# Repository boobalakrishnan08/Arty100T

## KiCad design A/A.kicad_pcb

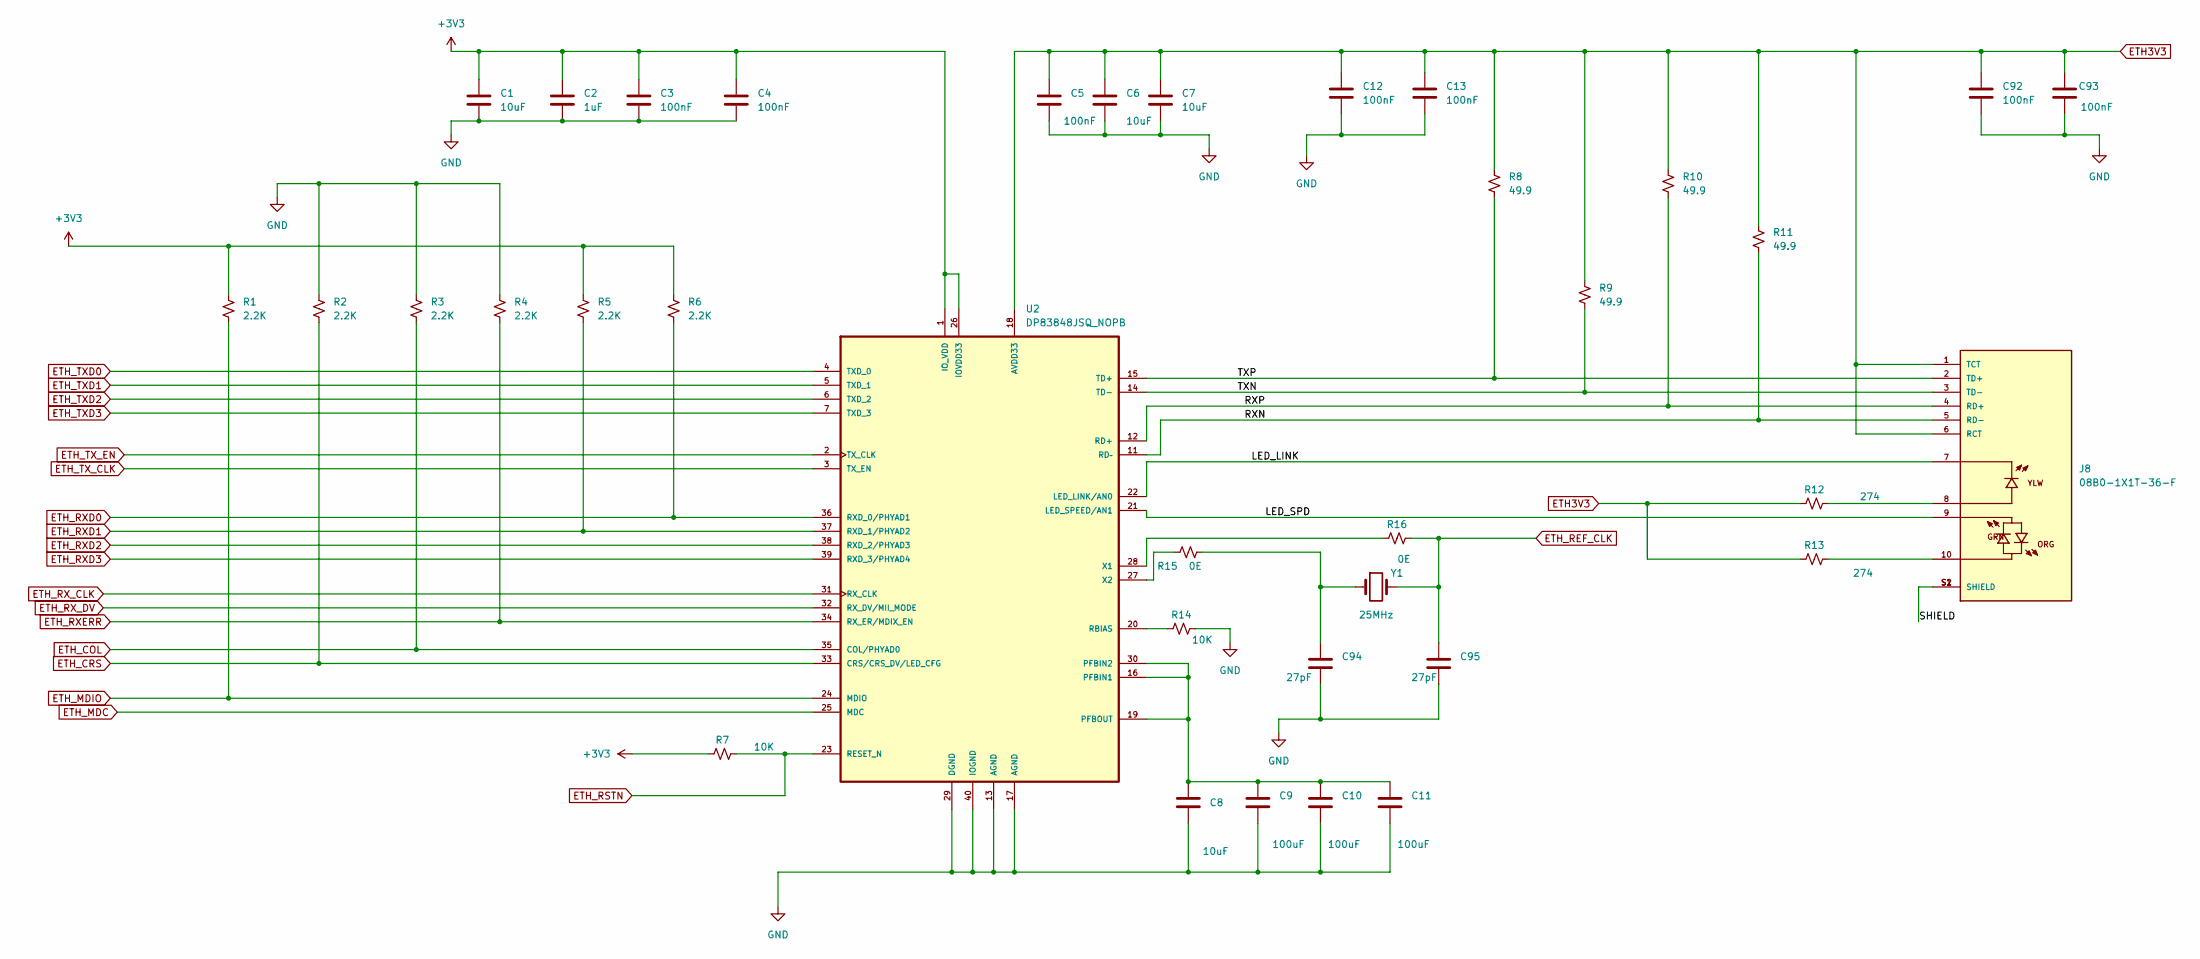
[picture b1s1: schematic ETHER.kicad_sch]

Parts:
C1: 10uF; C_1206_3216Metric
C2: 1uF; C_0805_2012Metric
C3, C4, C5, C12, C13, C92, C93: 100nF; C_1206_3216Metric
C6, C7, C8: 10uF; C_0805_2012Metric
C9, C10, C11: 100uF; C_1206_3216Metric
C94, C95: 27pF; C_0603_1608Metric
J8: 08B0-1X1T-36-F; BEL_08B0-1X1T-36-F; PARTREV D
R1, R2, R3, R4, R5, R6: 2.2K; R_0402_1005Metric
R7, R14: 10K; R_0402_1005Metric
R8, R9, R10, R11: 49.9; R_0402_1005Metric
R12, R13: 274; R_0402_1005Metric
R15, R16: 0E; R_0402_1005Metric
U2: DP83848JSQ_NOPB; XCVR_DP83848JSQ_NOPB; PARTREV APR 2015; DigiKey_Part_Number DP83848JSQ/NOPBTR-ND
Y1: 25MHz; Crystal_SMD_SeikoEpson_FA128-4Pin_2.0x1.6mm

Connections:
+3V3: C1.1, C2.1, C3.1, C4.1, R1.1, R5.1, R6.1, R7.1, U2.1 (IO_VDD), U2.26 (IOVDD33); also elsewhere on the board
/ETHER/LED_LINK: J8.7, U2.22 (LED_LINK/AN0)
/ETHER/LED_SPD: J8.9, U2.21 (LED_SPEED/AN1)
/ETHER/RXN: J8.5 (RD-), R11.2, U2.11 (RD–)
/ETHER/RXP: J8.4 (RD+), R10.2, U2.12 (RD+)
/ETHER/SHIELD: J8.S1 (SHIELD), J8.S2 (SHIELD)
/ETHER/TXN: J8.3 (TD-), R9.2, U2.14 (TD-)
/ETHER/TXP: J8.2 (TD+), R8.2, U2.15 (TD+)
ETH3V3: C5.1, C6.1, C7.1, C12.1, C13.1, C92.1, C93.1, J8.1 (TCT), J8.6 (RCT), R8.1, R9.1, R10.1, R11.1, R12.1, R13.1, U2.18 (AVDD33)
ETH_COL: R3.2, U2.35 (COL/PHYAD0); also elsewhere on the board
ETH_CRS: R2.2, U2.33 (CRS/CRS_DV/LED_CFG); also elsewhere on the board
ETH_MDC: U2.25 (MDC); also elsewhere on the board
ETH_MDIO: R1.2, U2.24 (MDIO); also elsewhere on the board
ETH_REF_CLK: C95.1, R16.2, Y1.2; also elsewhere on the board
ETH_RSTN: R7.2, U2.23 (RESET_N); also elsewhere on the board
ETH_RXD0: R6.2, U2.36 (RXD_0/PHYAD1); also elsewhere on the board
ETH_RXD1: R5.2, U2.37 (RXD_1/PHYAD2); also elsewhere on the board
ETH_RXD2: U2.38 (RXD_2/PHYAD3); also elsewhere on the board
ETH_RXD3: U2.39 (RXD_3/PHYAD4); also elsewhere on the board
ETH_RXERR: R4.2, U2.34 (RX_ER/MDIX_EN); also elsewhere on the board
ETH_RX_CLK: U2.31 (RX_CLK); also elsewhere on the board
ETH_RX_DV: U2.32 (RX_DV/MII_MODE); also elsewhere on the board
ETH_TXD0: U2.4 (TXD_0); also elsewhere on the board
ETH_TXD1: U2.5 (TXD_1); also elsewhere on the board
ETH_TXD2: U2.6 (TXD_2); also elsewhere on the board
ETH_TXD3: U2.7 (TXD_3); also elsewhere on the board
ETH_TX_CLK: U2.3 (TX_EN); also elsewhere on the board
ETH_TX_EN: U2.2 (TX_CLK); also elsewhere on the board
GND: C1.2, C2.2, C3.2, C4.2, C5.2, C6.2, C7.2, C8.2, C9.2, C10.2, C11.2, C12.2, C13.2, C92.2, C93.2, C94.2, C95.2, R2.1, R3.1, R4.1, R14.2, U2.13 (AGND), U2.17 (AGND), U2.29 (DGND), U2.40 (IOGND); also elsewhere on the board
unnamed: C94.1, R15.2, Y1.1
unnamed: J8.8, R12.2
unnamed: J8.10, R13.2
unnamed: C8.1, C9.1, C10.1, C11.1, U2.16 (PFBIN1), U2.19 (PFBOUT), U2.30 (PFBIN2)
unnamed: R14.1, U2.20 (RBIAS)
unnamed: R16.1, U2.28 (X1)
unnamed: R15.1, U2.27 (X2)

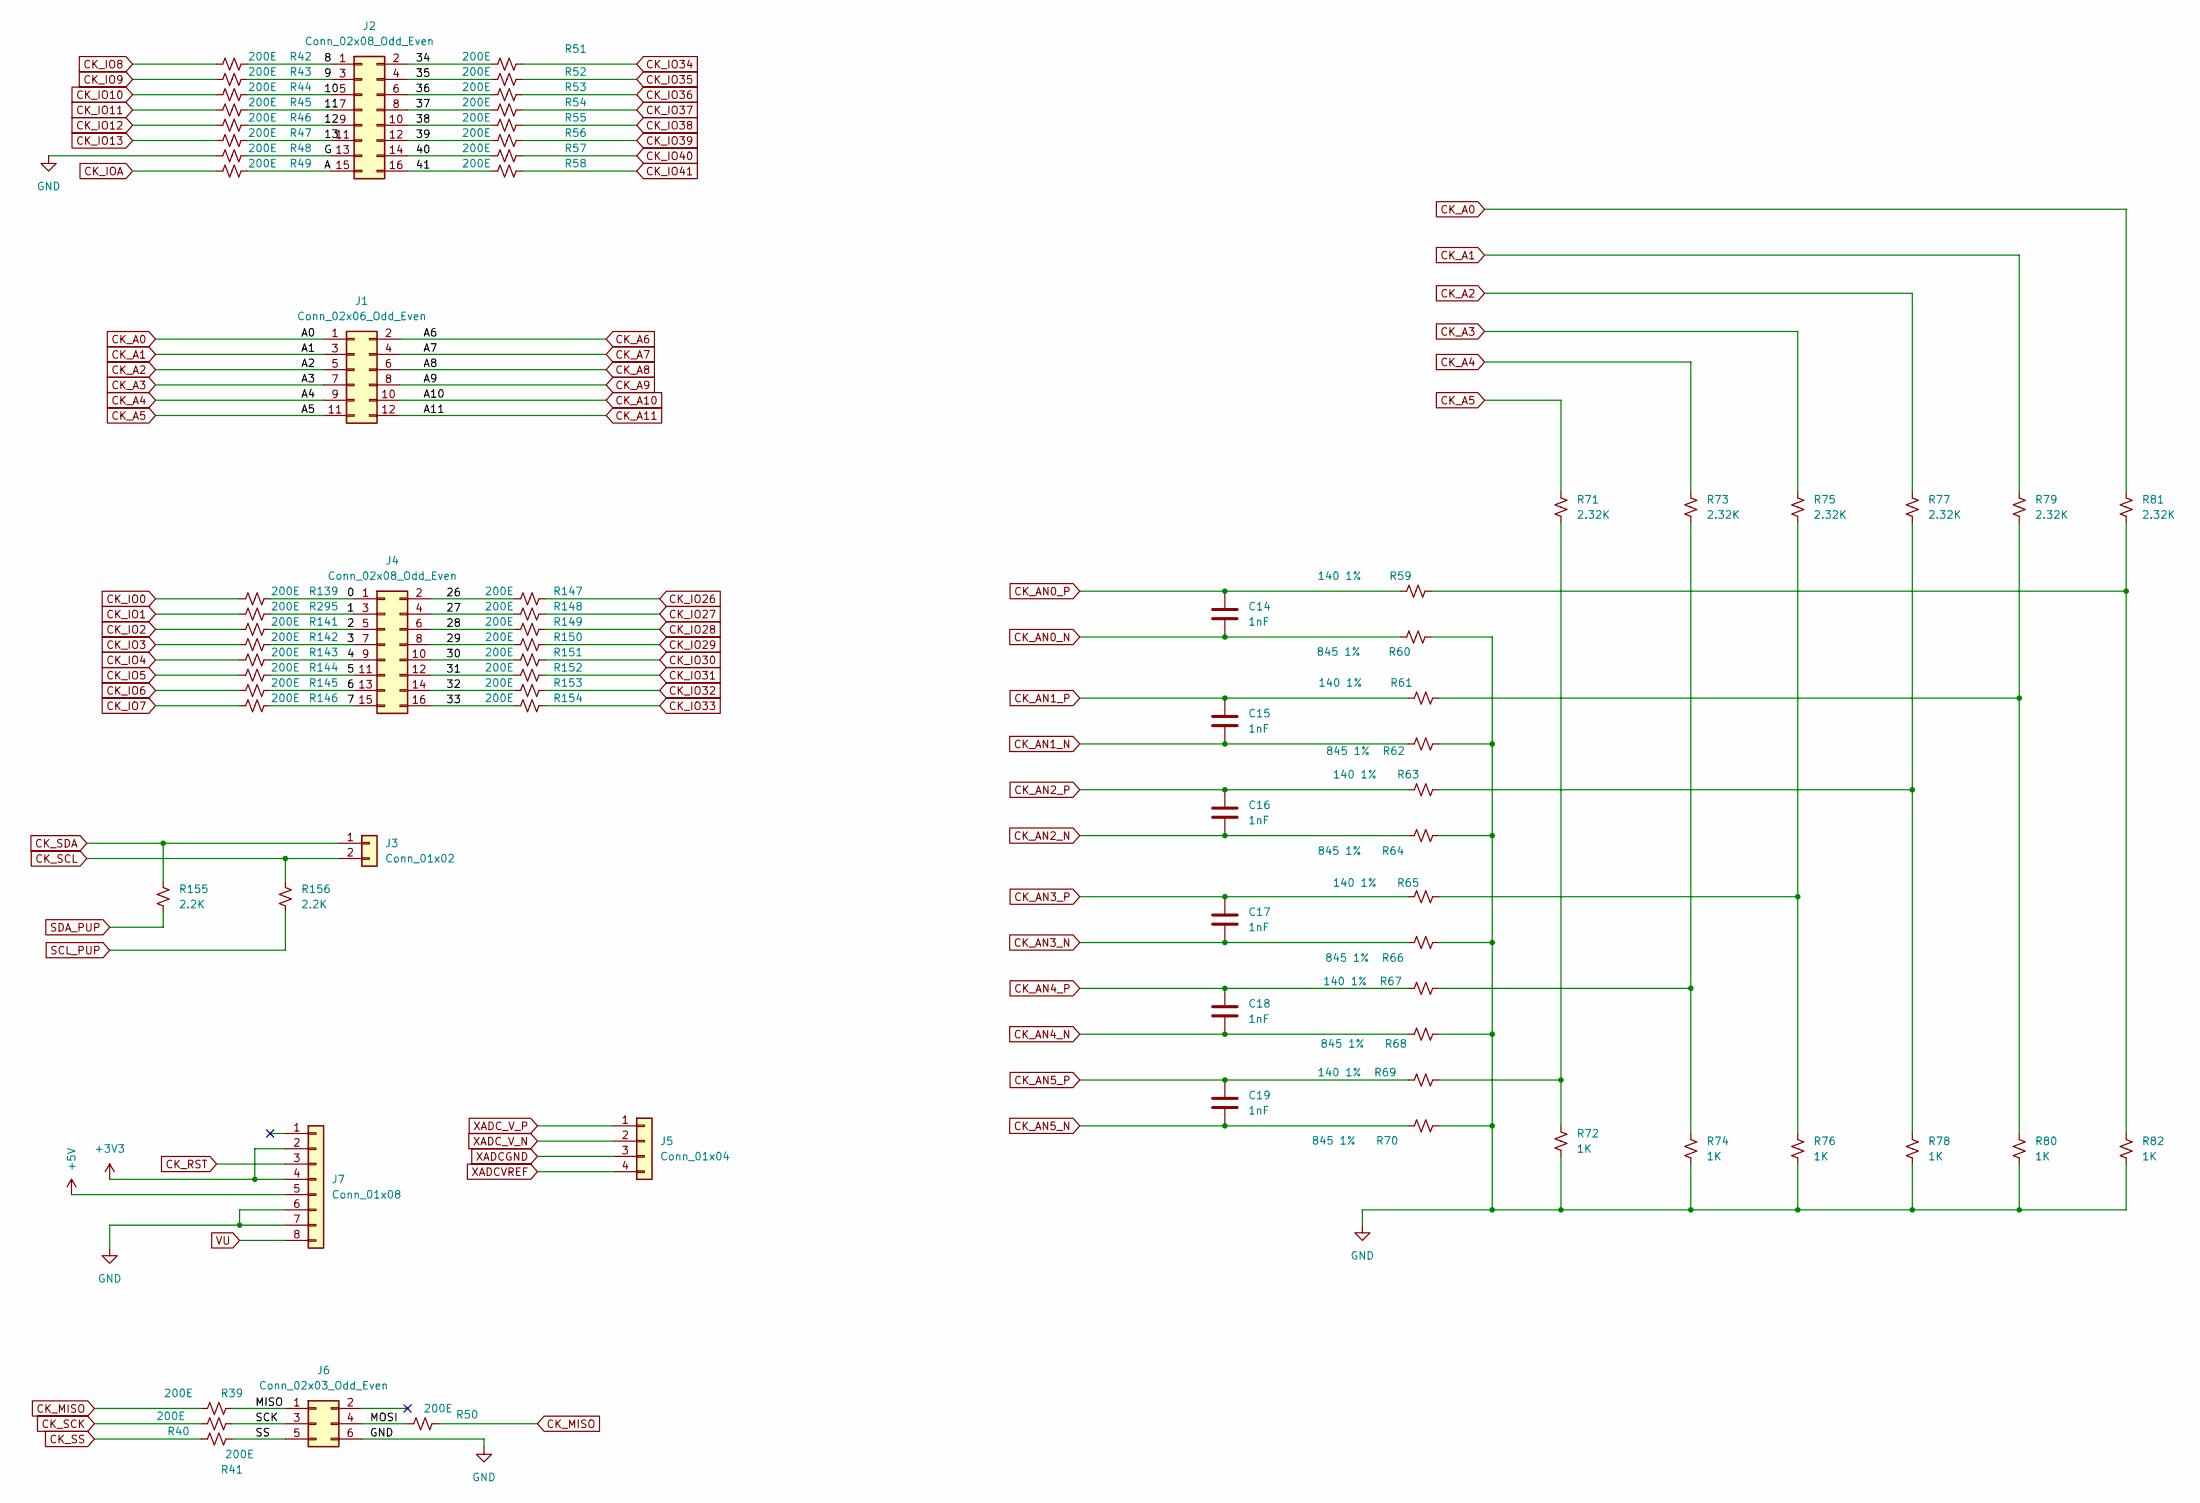
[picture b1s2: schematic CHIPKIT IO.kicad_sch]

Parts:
C14, C15, C16, C17, C18, C19: 1nF; C_0805_2012Metric
J1: Conn_02x06_Odd_Even; PinSocket_2x06_P2.54mm_Vertical
J2, J4: Conn_02x08_Odd_Even; PinSocket_2x08_P2.54mm_Vertical
J3: Conn_01x02; PinSocket_2x01_P2.54mm_Vertical
J5: Conn_01x04; PinSocket_1x04_P2.54mm_Vertical
J6: Conn_02x03_Odd_Even; PinSocket_2x03_P2.54mm_Vertical
J7: Conn_01x08; PinSocket_1x08_P2.54mm_Vertical
R39, R40, R41, R42, R43, R44, R45, R46, R47, R48, R49, R50, R51, R52, R53, R54, R55, R56, R57, R58, R139, R141, R142, R143, R144, R145, R146, R147, R148, R149, R150, R151, R152, R153, R154, R295: 200E; R_0402_1005Metric
R59, R61, R63, R65, R67, R69: 140 1%; R_0402_1005Metric
R60, R62, R64, R66, R68, R70: 845 1%; R_0402_1005Metric
R71, R73, R75, R77, R79, R81: 2.32K; R_0402_1005Metric
R72, R74, R76, R78, R80, R82: 1K; R_0402_1005Metric
R155, R156: 2.2K; R_0402_1005Metric

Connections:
+3V3: J7.2, J7.4; also elsewhere on the board
+5V: J7.5; also elsewhere on the board
/CHIPKIT IO/0: J4.1, R139.2
/CHIPKIT IO/1: J4.3, R295.2
/CHIPKIT IO/2: J4.5, R141.2
/CHIPKIT IO/3: J4.7, R142.2
/CHIPKIT IO/4: J4.9, R143.2
/CHIPKIT IO/5: J4.11, R144.2
/CHIPKIT IO/6: J4.13, R145.2
/CHIPKIT IO/7: J4.15, R146.2
/CHIPKIT IO/8: J2.1, R42.2
/CHIPKIT IO/9: J2.3, R43.2
/CHIPKIT IO/10: J2.5, R44.2
/CHIPKIT IO/11: J2.7, R45.2
/CHIPKIT IO/12: J2.9, R46.2
/CHIPKIT IO/13: J2.11, R47.2
/CHIPKIT IO/26: J4.2, R147.1
/CHIPKIT IO/27: J4.4, R148.1
/CHIPKIT IO/28: J4.6, R149.1
/CHIPKIT IO/29: J4.8, R150.1
/CHIPKIT IO/30: J4.10, R151.1
/CHIPKIT IO/31: J4.12, R152.1
/CHIPKIT IO/32: J4.14, R153.1
/CHIPKIT IO/33: J4.16, R154.1
/CHIPKIT IO/34: J2.2, R51.1
/CHIPKIT IO/35: J2.4, R52.1
/CHIPKIT IO/36: J2.6, R53.1
/CHIPKIT IO/37: J2.8, R54.1
/CHIPKIT IO/38: J2.10, R55.1
/CHIPKIT IO/39: J2.12, R56.1
/CHIPKIT IO/40: J2.14, R57.1
/CHIPKIT IO/41: J2.16, R58.1
/CHIPKIT IO/A: J2.15, R49.2
/CHIPKIT IO/G: J2.13, R48.2
/CHIPKIT IO/MISO: J6.1, R39.2
/CHIPKIT IO/MOSI: J6.4, R50.1
/CHIPKIT IO/SCK: J6.3, R40.2
/CHIPKIT IO/SS: J6.5, R41.2
CK_A0: J1.1, R81.1; also elsewhere on the board
CK_A1: J1.3, R79.1; also elsewhere on the board
CK_A2: J1.5, R77.1; also elsewhere on the board
CK_A3: J1.7, R75.1; also elsewhere on the board
CK_A4: J1.9, R73.1; also elsewhere on the board
CK_A5: J1.11, R71.1; also elsewhere on the board
CK_A6: J1.2; also elsewhere on the board
CK_A7: J1.4; also elsewhere on the board
CK_A8: J1.6; also elsewhere on the board
CK_A9: J1.8; also elsewhere on the board
CK_A10: J1.10; also elsewhere on the board
CK_A11: J1.12; also elsewhere on the board
CK_AN0_N: C14.2, R60.1; also elsewhere on the board
CK_AN0_P: C14.1, R59.1; also elsewhere on the board
CK_AN1_N: C15.2, R62.1; also elsewhere on the board
CK_AN1_P: C15.1, R61.1; also elsewhere on the board
CK_AN2_N: C16.2, R64.1; also elsewhere on the board
CK_AN2_P: C16.1, R63.1; also elsewhere on the board
CK_AN3_N: C17.2, R66.1; also elsewhere on the board
CK_AN3_P: C17.1, R65.1; also elsewhere on the board
CK_AN4_N: C18.2, R68.1; also elsewhere on the board
CK_AN4_P: C18.1, R67.1; also elsewhere on the board
CK_AN5_N: C19.2, R70.1; also elsewhere on the board
CK_AN5_P: C19.1, R69.1; also elsewhere on the board
CK_IO0: R139.1; also elsewhere on the board
CK_IO1: R295.1; also elsewhere on the board
CK_IO2: R141.1; also elsewhere on the board
CK_IO3: R142.1; also elsewhere on the board
CK_IO4: R143.1; also elsewhere on the board
CK_IO5: R144.1; also elsewhere on the board
CK_IO6: R145.1; also elsewhere on the board
CK_IO7: R146.1; also elsewhere on the board
CK_IO8: R42.1; also elsewhere on the board
CK_IO9: R43.1; also elsewhere on the board
CK_IO10: R44.1; also elsewhere on the board
CK_IO11: R45.1; also elsewhere on the board
CK_IO12: R46.1; also elsewhere on the board
CK_IO13: R47.1; also elsewhere on the board
CK_IO26: R147.2; also elsewhere on the board
CK_IO27: R148.2; also elsewhere on the board
CK_IO28: R149.2; also elsewhere on the board
CK_IO29: R150.2; also elsewhere on the board
CK_IO30: R151.2; also elsewhere on the board
CK_IO31: R152.2; also elsewhere on the board
CK_IO32: R153.2; also elsewhere on the board
CK_IO33: R154.2; also elsewhere on the board
CK_IO34: R51.2; also elsewhere on the board
CK_IO35: R52.2; also elsewhere on the board
CK_IO36: R53.2; also elsewhere on the board
CK_IO37: R54.2; also elsewhere on the board
CK_IO38: R55.2; also elsewhere on the board
CK_IO39: R56.2; also elsewhere on the board
CK_IO40: R57.2; also elsewhere on the board
CK_IO41: R58.2; also elsewhere on the board
CK_IOA: R49.1; also elsewhere on the board
CK_MISO: R39.1, R50.2; also elsewhere on the board
CK_RST: J7.3; also elsewhere on the board
CK_SCK: R40.1; also elsewhere on the board
CK_SCL: J3.2, R156.1; also elsewhere on the board
CK_SDA: J3.1, R155.1; also elsewhere on the board
CK_SS: R41.1; also elsewhere on the board
GND: J6.6, J7.6, J7.7, R48.1, R60.2, R62.2, R64.2, R66.2, R68.2, R70.2, R72.2, R74.2, R76.2, R78.2, R80.2, R82.2; also elsewhere on the board
unnamed: R59.2, R81.2, R82.1
unnamed: R61.2, R79.2, R80.1
unnamed: R63.2, R77.2, R78.1
unnamed: R65.2, R75.2, R76.1
unnamed: R67.2, R73.2, R74.1
unnamed: R69.2, R71.2, R72.1
SCL_PUP: R156.2; also elsewhere on the board
SDA_PUP: R155.2; also elsewhere on the board
VU: J7.8; also elsewhere on the board
XADCGND: J5.3; also elsewhere on the board
XADCVREF: J5.4; also elsewhere on the board
XADC_V_N: J5.2; also elsewhere on the board
XADC_V_P: J5.1; also elsewhere on the board

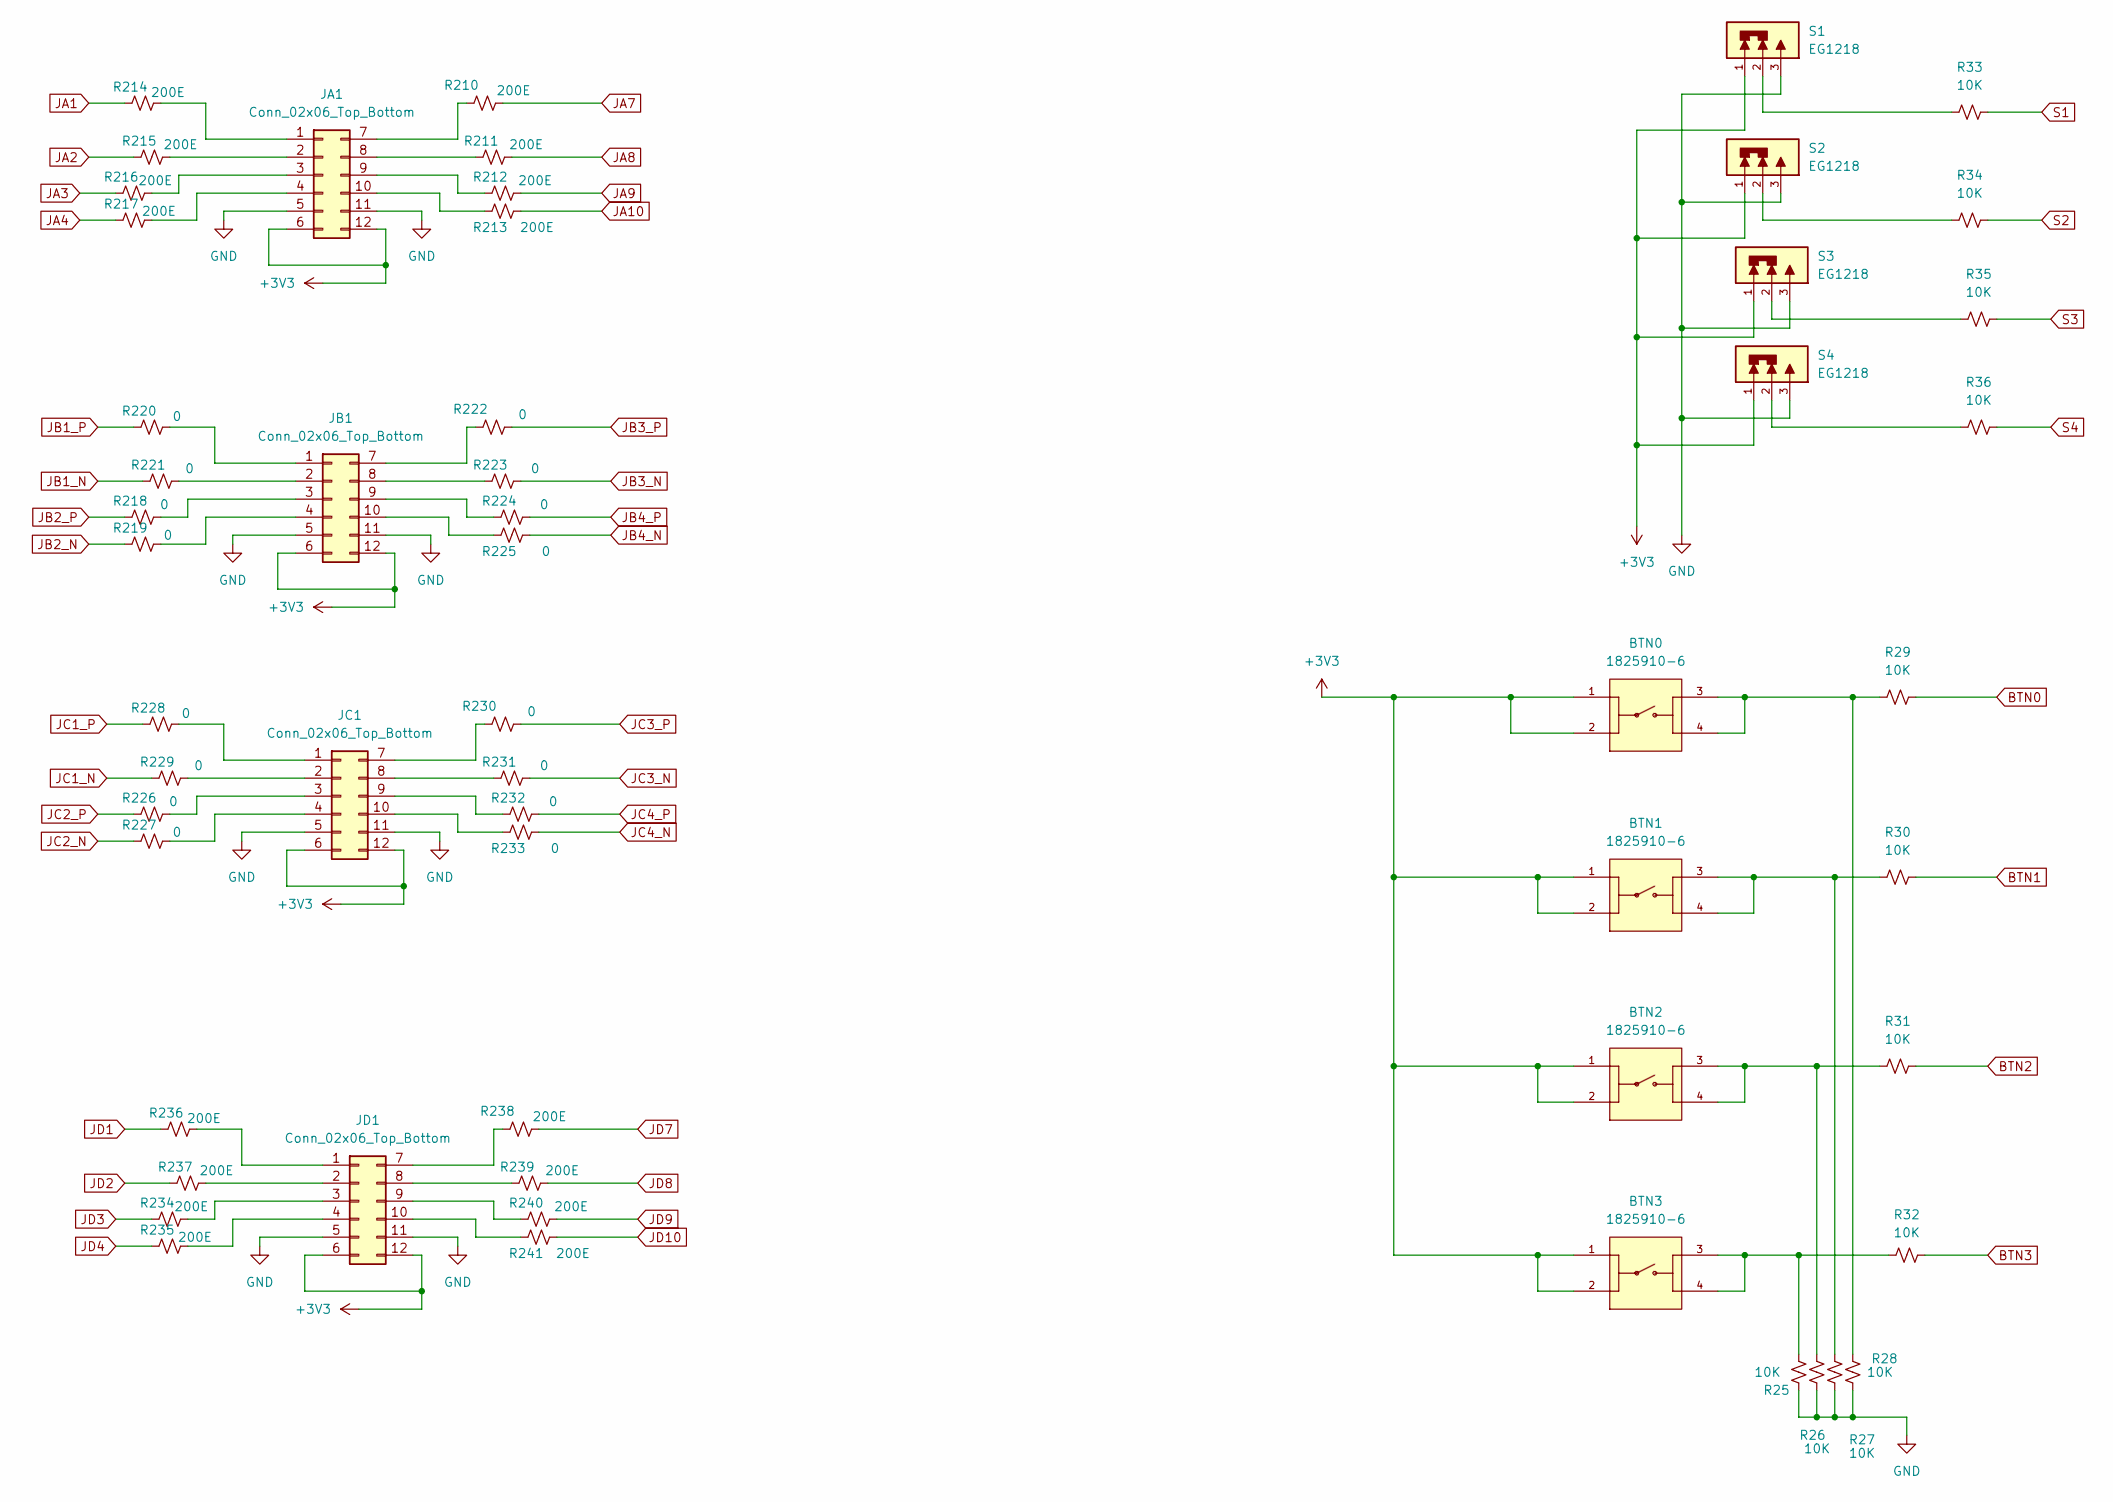
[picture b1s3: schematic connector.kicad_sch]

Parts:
BTN0, BTN1, BTN2, BTN3: 1825910-6; SW_1825910-6-4; PARTREV C10
JA1: Conn_02x06_Top_Bottom; PinSocket_2x06_P2.54mm_Horizontal
JB1: Conn_02x06_Top_Bottom; PinSocket_2x06_P2.54mm_Horizontal
JC1: Conn_02x06_Top_Bottom; PinSocket_2x06_P2.54mm_Horizontal
JD1: Conn_02x06_Top_Bottom; PinSocket_2x06_P2.54mm_Horizontal
R25, R26, R27, R28, R29, R30, R31, R32, R33, R34, R35, R36: 10K; R_0402_1005Metric
R210, R211, R212, R213, R214, R215, R216, R217, R234, R235, R236, R237, R238, R239, R240, R241: 200E; R_0402_1005Metric
R218, R219, R220, R221, R222, R223, R224, R225, R226, R227, R228, R229, R230, R231, R232, R233: 0; R_0402_1005Metric
S1, S2, S3, S4: EG1218; SW_EG1218

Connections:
+3V3: BTN0.1, BTN0.2, BTN1.1, BTN1.2, BTN2.1, BTN2.2, BTN3.1, BTN3.2, JA1.6, JA1.12, JB1.6, JB1.12, JC1.6, JC1.12, JD1.6, JD1.12, S1.1, S2.1, S3.1, S4.1; also elsewhere on the board
BTN0: R29.2; also elsewhere on the board
BTN1: R30.2; also elsewhere on the board
BTN2: R31.2; also elsewhere on the board
BTN3: R32.2; also elsewhere on the board
GND: JA1.5, JA1.11, JB1.5, JB1.11, JC1.5, JC1.11, JD1.5, JD1.11, R25.1, R26.1, R27.1, R28.1, S1.3, S2.3, S3.3, S4.3; also elsewhere on the board
JA1: R214.1; also elsewhere on the board
JA2: R215.1; also elsewhere on the board
JA3: R216.1; also elsewhere on the board
JA4: R217.1; also elsewhere on the board
JA7: R210.2; also elsewhere on the board
JA8: R211.2; also elsewhere on the board
JA9: R212.2; also elsewhere on the board
JA10: R213.2; also elsewhere on the board
JB1_N: R221.1; also elsewhere on the board
JB1_P: R220.1; also elsewhere on the board
JB2_N: R219.1; also elsewhere on the board
JB2_P: R218.1; also elsewhere on the board
JB3_N: R223.2; also elsewhere on the board
JB3_P: R222.2; also elsewhere on the board
JB4_N: R225.2; also elsewhere on the board
JB4_P: R224.2; also elsewhere on the board
JC1_N: R229.1; also elsewhere on the board
JC1_P: R228.1; also elsewhere on the board
JC2_N: R227.1; also elsewhere on the board
JC2_P: R226.1; also elsewhere on the board
JC3_N: R231.2; also elsewhere on the board
JC3_P: R230.2; also elsewhere on the board
JC4_N: R233.2; also elsewhere on the board
JC4_P: R232.2; also elsewhere on the board
JD1: R236.1; also elsewhere on the board
JD2: R237.1; also elsewhere on the board
JD3: R234.1; also elsewhere on the board
JD4: R235.1; also elsewhere on the board
JD7: R238.2; also elsewhere on the board
JD8: R239.2; also elsewhere on the board
JD9: R240.2; also elsewhere on the board
JD10: R241.2; also elsewhere on the board
unnamed: BTN0.3, BTN0.4, R28.2, R29.1
unnamed: BTN1.3, BTN1.4, R27.2, R30.1
unnamed: BTN2.3, BTN2.4, R26.2, R31.1
unnamed: BTN3.3, BTN3.4, R25.2, R32.1
unnamed: JA1.1, R214.2
unnamed: JA1.2, R215.2
unnamed: JA1.3, R216.2
unnamed: JA1.4, R217.2
unnamed: JA1.7, R210.1
unnamed: JA1.8, R211.1
unnamed: JA1.9, R212.1
unnamed: JA1.10, R213.1
unnamed: JB1.1, R220.2
unnamed: JB1.2, R221.2
unnamed: JB1.3, R218.2
unnamed: JB1.4, R219.2
unnamed: JB1.7, R222.1
unnamed: JB1.8, R223.1
unnamed: JB1.9, R224.1
unnamed: JB1.10, R225.1
unnamed: JC1.1, R228.2
unnamed: JC1.2, R229.2
unnamed: JC1.3, R226.2
unnamed: JC1.4, R227.2
unnamed: JC1.7, R230.1
unnamed: JC1.8, R231.1
unnamed: JC1.9, R232.1
unnamed: JC1.10, R233.1
unnamed: JD1.1, R236.2
unnamed: JD1.2, R237.2
unnamed: JD1.3, R234.2
unnamed: JD1.4, R235.2
unnamed: JD1.7, R238.1
unnamed: JD1.8, R239.1
unnamed: JD1.9, R240.1
unnamed: JD1.10, R241.1
unnamed: R33.1, S1.2
unnamed: R34.1, S2.2
unnamed: R35.1, S3.2
unnamed: R36.1, S4.2
S1: R33.2; also elsewhere on the board
S2: R34.2; also elsewhere on the board
S3: R35.2; also elsewhere on the board
S4: R36.2; also elsewhere on the board
